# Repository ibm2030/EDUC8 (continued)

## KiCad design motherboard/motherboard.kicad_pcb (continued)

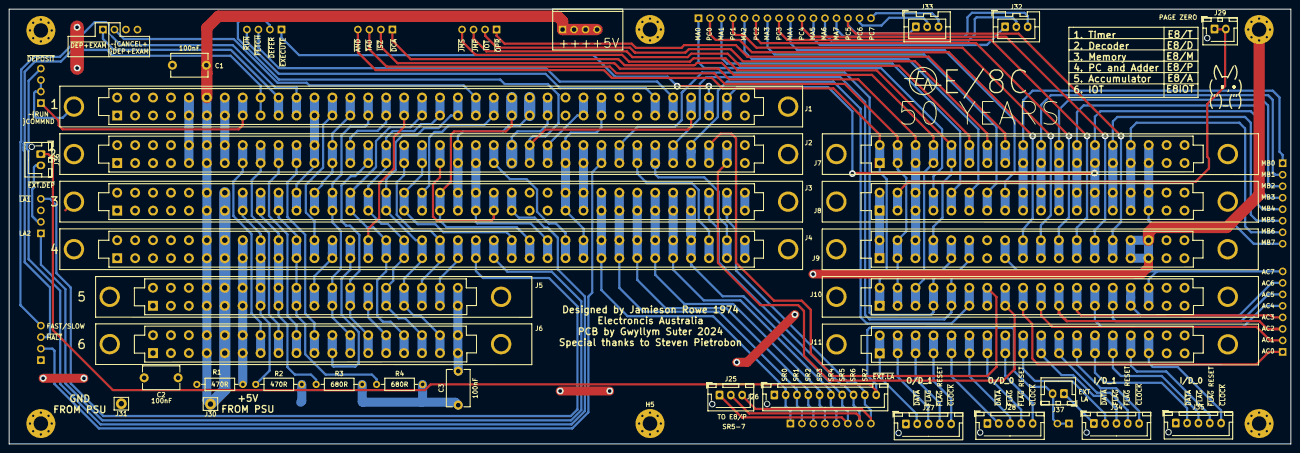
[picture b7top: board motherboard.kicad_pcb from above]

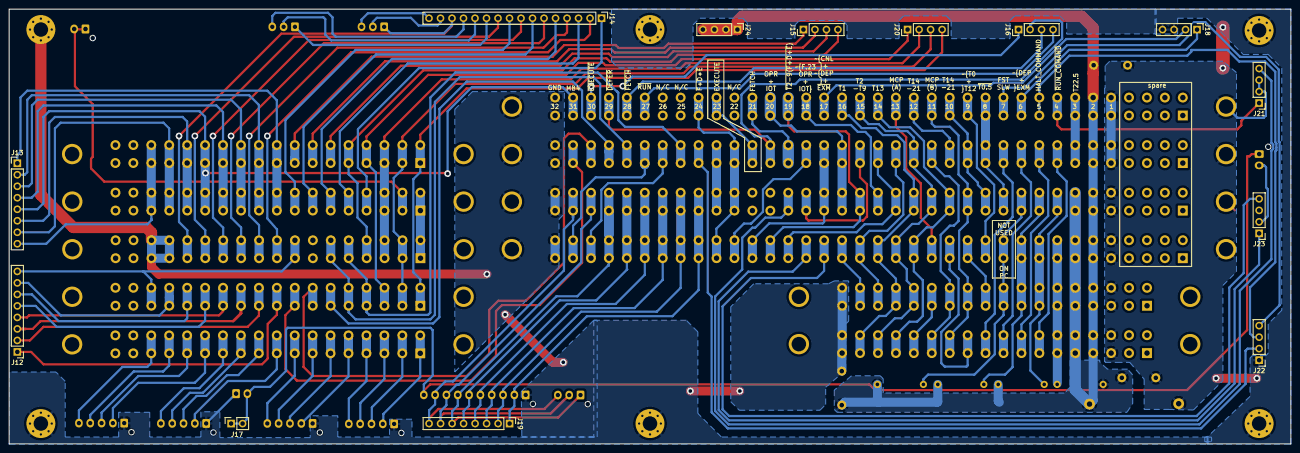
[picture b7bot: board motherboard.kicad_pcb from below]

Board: 2 copper layers, 283.0 x 96.0 mm, 50 parts (13 on the bottom side), 125 nets.

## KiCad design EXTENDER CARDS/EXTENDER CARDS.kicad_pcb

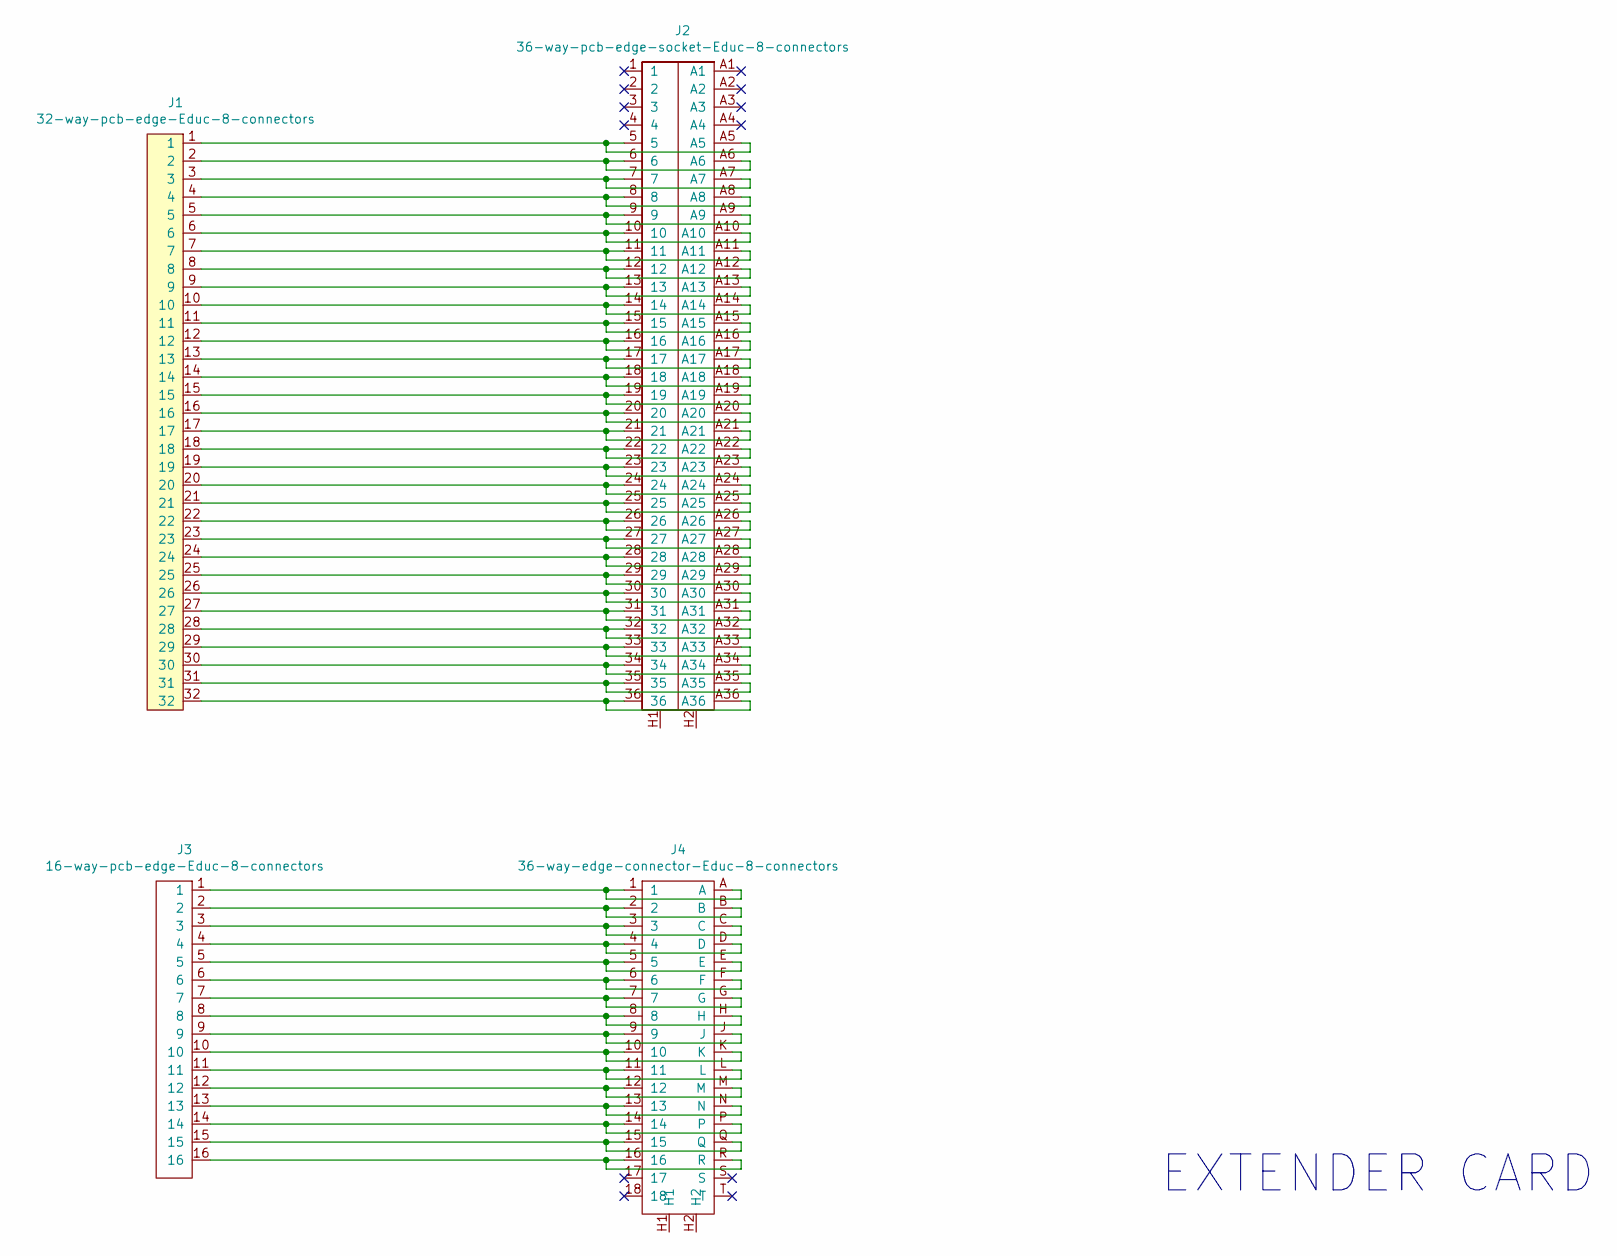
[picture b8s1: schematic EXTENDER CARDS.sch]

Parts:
J1: 32-way-pcb-edge-Educ-8-connectors; PCB_32pin
J2: 36-way-pcb-edge-socket-Educ-8-connectors; 72_way_3.96mm_card_edge_socket
J3: 16-way-pcb-edge-Educ-8-connectors; PCB_16pin
J4: 36-way-edge-connector-Educ-8-connectors; 36_way_3.96mm_card_edge_socket

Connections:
unnamed: J1.1, J2.5, J2.A5
unnamed: J1.2, J2.6, J2.A6
unnamed: J1.3, J2.7, J2.A7
unnamed: J1.4, J2.8, J2.A8
unnamed: J1.5, J2.9, J2.A9
unnamed: J1.6, J2.10, J2.A10
unnamed: J1.7, J2.11, J2.A11
unnamed: J1.8, J2.12, J2.A12
unnamed: J1.9, J2.13, J2.A13
unnamed: J1.10, J2.14, J2.A14
unnamed: J1.11, J2.15, J2.A15
unnamed: J1.12, J2.16, J2.A16
unnamed: J1.13, J2.17, J2.A17
unnamed: J1.14, J2.18, J2.A18
unnamed: J1.15, J2.19, J2.A19
unnamed: J1.16, J2.20, J2.A20
unnamed: J1.17, J2.21, J2.A21
unnamed: J1.18, J2.22, J2.A22
unnamed: J1.19, J2.23, J2.A23
unnamed: J1.20, J2.24, J2.A24
unnamed: J1.21, J2.25, J2.A25
unnamed: J1.22, J2.26, J2.A26
unnamed: J1.23, J2.27, J2.A27
unnamed: J1.24, J2.28, J2.A28
unnamed: J1.25, J2.29, J2.A29
unnamed: J1.26, J2.30, J2.A30
unnamed: J1.27, J2.31, J2.A31
unnamed: J1.28, J2.32, J2.A32
unnamed: J1.29, J2.33, J2.A33
unnamed: J1.30, J2.34, J2.A34
unnamed: J1.31, J2.35, J2.A35
unnamed: J1.32, J2.36, J2.A36
unnamed: J3.1, J4.1, J4.A
unnamed: J3.2, J4.2, J4.B
unnamed: J3.3, J4.3, J4.C
unnamed: J3.4, J4.4, J4.D
unnamed: J3.5, J4.5, J4.E
unnamed: J3.6, J4.6, J4.F
unnamed: J3.7, J4.7, J4.G
unnamed: J3.8, J4.8, J4.H
unnamed: J3.9, J4.9, J4.J
unnamed: J3.10, J4.10, J4.K
unnamed: J3.11, J4.11, J4.L
unnamed: J3.12, J4.12, J4.M
unnamed: J3.13, J4.13, J4.N
unnamed: J3.14, J4.14, J4.P
unnamed: J3.15, J4.15, J4.Q
unnamed: J3.16, J4.16, J4.R
unnamed: J4.17, J4.S
unnamed: J4.18, J4.T

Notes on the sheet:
EXTENDER CARD

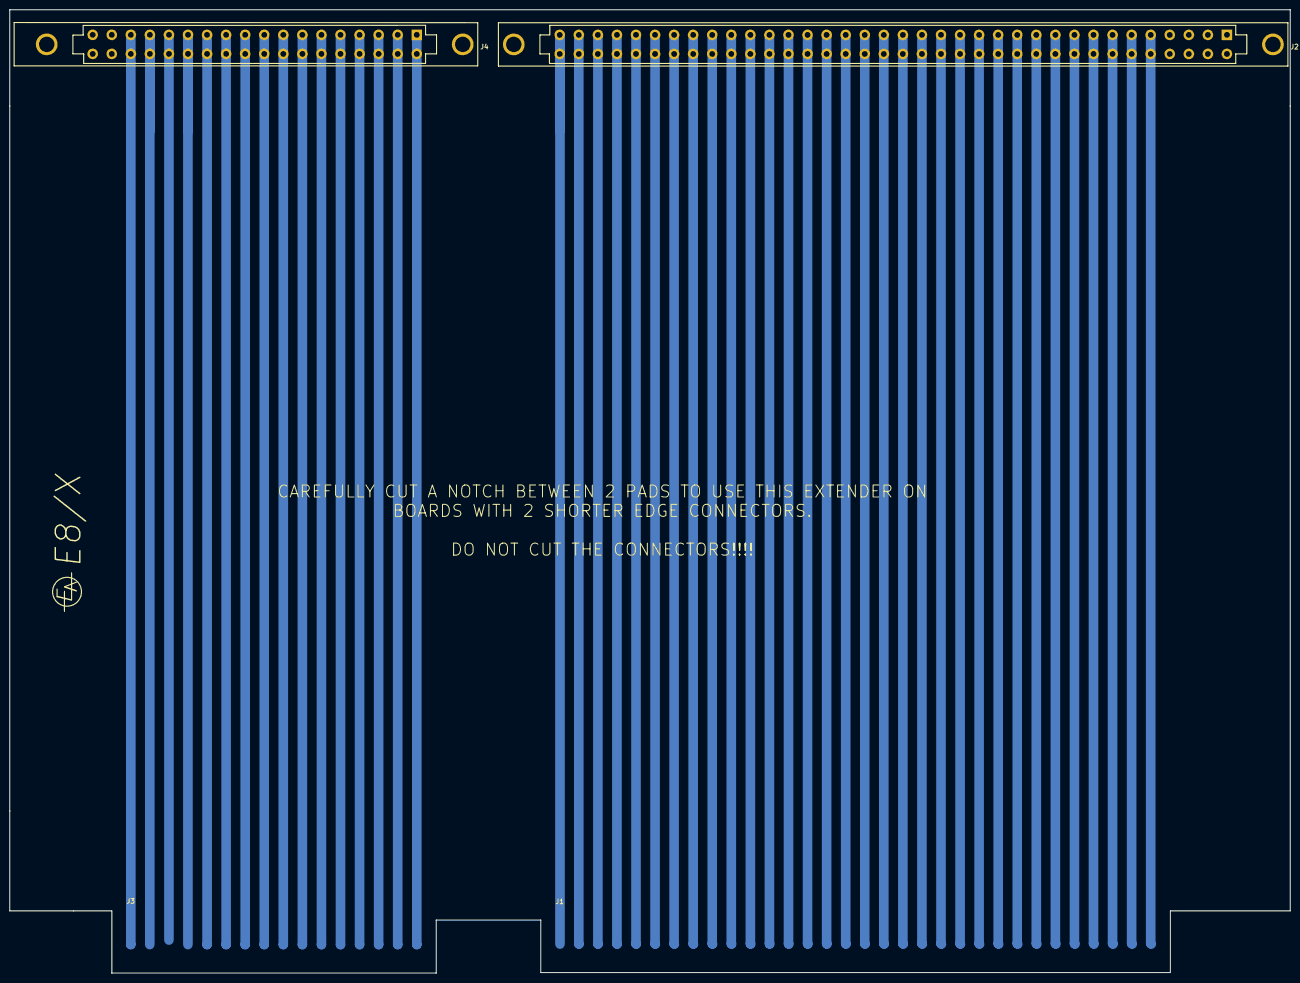
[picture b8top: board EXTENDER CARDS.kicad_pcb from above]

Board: 2 copper layers, 266.0 x 200.1 mm, 4 parts (0 on the bottom side), 50 nets.

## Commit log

2023-03-14 Create EDUC-8ME
2023-03-14 EDUC-8ME 13/3/2023
2023-03-14 EDUC-8ME 14/3/2023
2023-04-08 New PCB with all the corrections made
2024-04-01 Schematic update for 9001/74105 to 74LS74
2024-04-01 Schematic fixes
2024-06-13 Schematic update 2024-04-14 plus fixes
2024-06-13 Schematic update 2024-04-14 done
2024-06-29 EDUC-8ME update:\nI've made a fairly large update to EDUC-8ME, a memory and I/O port expansion for EDUC-8. I have moved the unit selection and address decoding logic from E8ME/D to E8ME/I. This means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
2024-09-08 EDUC-8ME update from Steven Pietrobon
2024-10-30 EDUC-8L from Steven Pietrobon http://www.sworld.com.au/steven/educ-8/educ-8l.pdf
2025-07-23 Changes 20-7-2025 E8/T. Connected 3 missing supply rail tracks to ICS Added flood fill top and bottom to reduce noise E8/F Corrected labelling on RHS board to reflect EXT_LA not GND Changed fast slow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
2025-08-27 128x16 RAM V5 update
2026-05-27 | Section | Change | |---------|--------| | 1.1 | Added output file behavior | | 4 | Replaced all number formats with single rule: `o` = octal, bare = decimal | | 7.3 | All IOT mnemonics now include 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
2026-05-28 There was a bug inadvertently created with the previous compiler, it didn’t detect the 16 byte page crossing boundary and this was fixed. Secondly, the uploader start and main address were in decimal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
